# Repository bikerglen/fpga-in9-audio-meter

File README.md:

# fpga-in9-audio-meter
<p>Clone repo to convenient location</p>
<p>Launch Vivado 2018.2</p>
<p>In TCL console:</p>
<p>cd [path to create project]</p>
<p>source [path to repo]/vivado/create-project.tcl</p>
<p>generate bitstream</p>
<p>export hardware / local / do not include bitstream</p>
<p>launch sdk</p>
<p>create new xilinx standalone hello world application</p>
<p>replace helloworld C code with contents of sdk-c/helloworld.c</p>
<p>add 'm' to helloworld -> properties -> C/C++ Build -> Settings -> Libraries
</p>
<p>to do: rewrite cordic using generate loops</p>

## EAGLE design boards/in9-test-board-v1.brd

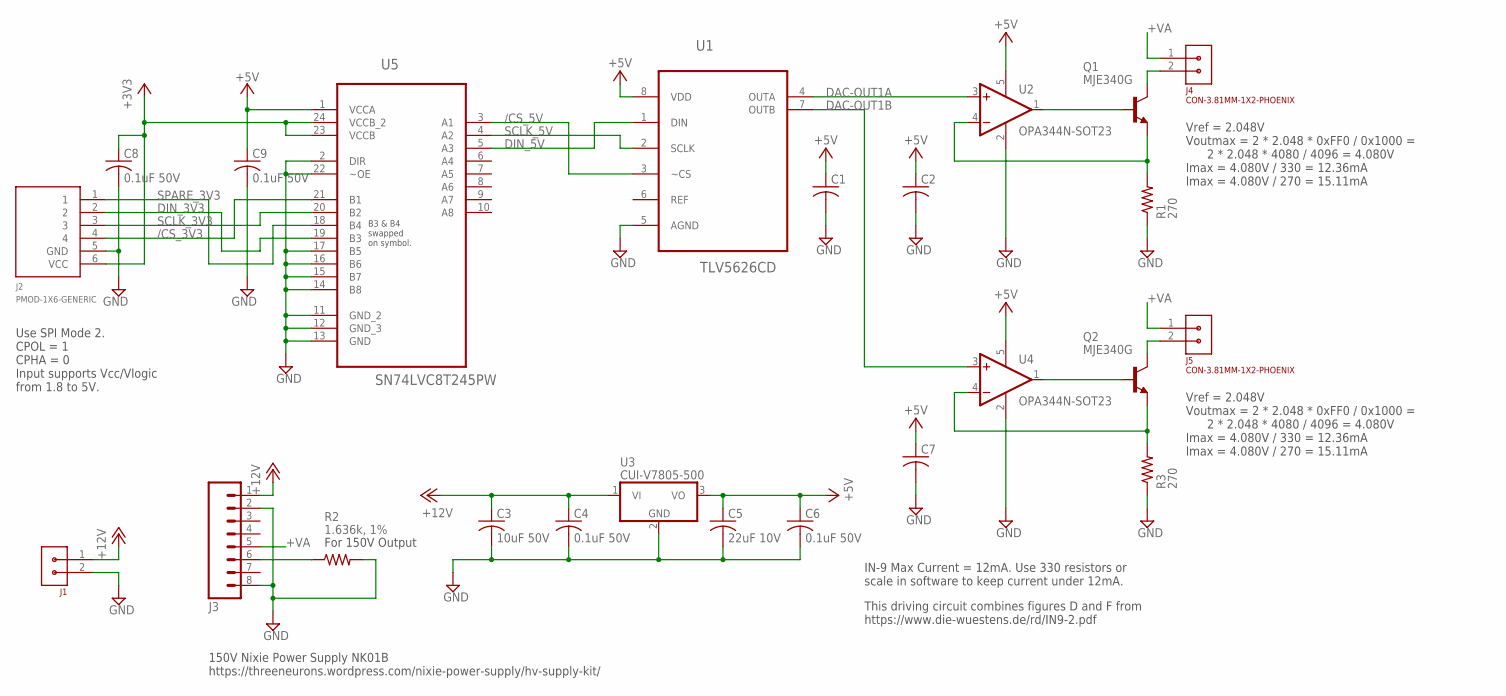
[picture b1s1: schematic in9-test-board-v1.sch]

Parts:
C1, C2, C7: C-USC1206K; C1206K
C3: 10uF 50V; C1210K; MFR_PART_NO C1210C106K5RACTU
C4, C6, C8, C9: 0.1uF 50V; C1206K; MFR_PART_NO C1206S104M5RACTU
C5: 22uF 10V; C1206K; MFR_PART_NO C1206C226K8RAC7800
J1: CON-3.81MM-1X2-PHOENIX-1803426; CON-PHOENIX-1803426-3.81-1X2
J2: PMOD-1X6-GENERIC; CON-PMOD-1X6
J3: M08; 1X08
J4, J5: CON-3.81MM-1X2-PHOENIX; CON-PHOENIX-3.81-1X2-RA
Q1, Q2: MJE340G; TO126V
R1, R3: 270; R1206
R2: 1.636k, 1%; R1206
U1: TLV5626CD; SOIC127P600X175-8N
U2, U4: OPA344N-SOT23; SOT23-5
U3: CUI-V7805-500; CUI-78XX-500
U5: SN74LVC8T245PW; SOP65P640X120-24N

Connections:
+3V3: C8.1, J2.6 (VCC), U5.23 (VCCB), U5.24 (VCCB_2)
+5V: C1.1, C2.1, C5.1, C6.1, C7.1, C9.1, U1.8 (VDD), U2.5 (V+), U3.3 (VO), U4.5 (V+), U5.1 (VCCA)
+12V: C3.1, C4.1, J1.1, J3.1, U3.1 (VI)
+VA: J3.5, J4.1, J5.1
/CS_3V3: J2.4, U5.21 (B1)
/CS_5V: U1.3 (~CS), U5.3 (A1)
DAC-OUT1A: U1.4 (OUTA), U2.3 (+IN)
DAC-OUT1B: U1.7 (OUTB), U4.3 (+IN)
DIN_3V3: J2.2, U5.19 (B3)
DIN_5V: U1.1 (DIN), U5.5 (A3)
GND: C1.2, C2.2, C3.2, C4.2, C5.2, C6.2, C7.2, C8.2, C9.2, J1.2, J2.5 (GND), J3.2, J3.8, R1.1, R2.2, R3.1, U1.5 (AGND), U2.2 (V-), U3.2 (GND), U4.2 (V-), U5.2 (DIR), U5.11 (GND_2), U5.12 (GND_3), U5.13 (GND), U5.14 (B8), U5.15 (B7), U5.16 (B6), U5.17 (B5), U5.22 (~OE)
unnamed: Q1.1 (E), R1.2, U2.4 (-IN)
unnamed: Q1.3 (B), U2.1 (OUT)
unnamed: J3.6, R2.1
unnamed: Q2.1 (E), R3.2, U4.4 (-IN)
unnamed: Q2.3 (B), U4.1 (OUT)
OUT1A: J4.2, Q1.2 (C)
OUT1B: J5.2, Q2.2 (C)
SCLK_3V3: J2.3, U5.20 (B2)
SCLK_5V: U1.2 (SCLK), U5.4 (A2)
SPARE_3V3: J2.1, U5.18 (B4)

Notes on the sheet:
Vref = 2.048V Voutmax = 2 * 2.048 * 0xFF0 / 0x1000 = 2 * 2.048 * 4080 / 4096 = 4.080V Imax = 4.080V / 330 = 12.36mA Imax = 4.080V / 270 = 15.11mA
For 150V Output
150V Nixie Power Supply NK01B https://threeneurons.wordpress.com/nixie-power-supply/hv-supply-kit/
This driving circuit combines figures D and F from https://www.die-wuestens.de/rd/IN9-2.pdf
B3 & B4 swapped on symbol.
Use SPI Mode 2. CPOL = 1 CPHA = 0 Input supports Vcc/Vlogic from 1.8 to 5V.
IN-9 Max Current = 12mA. Use 330 resistors or scale in software to keep current under 12mA.

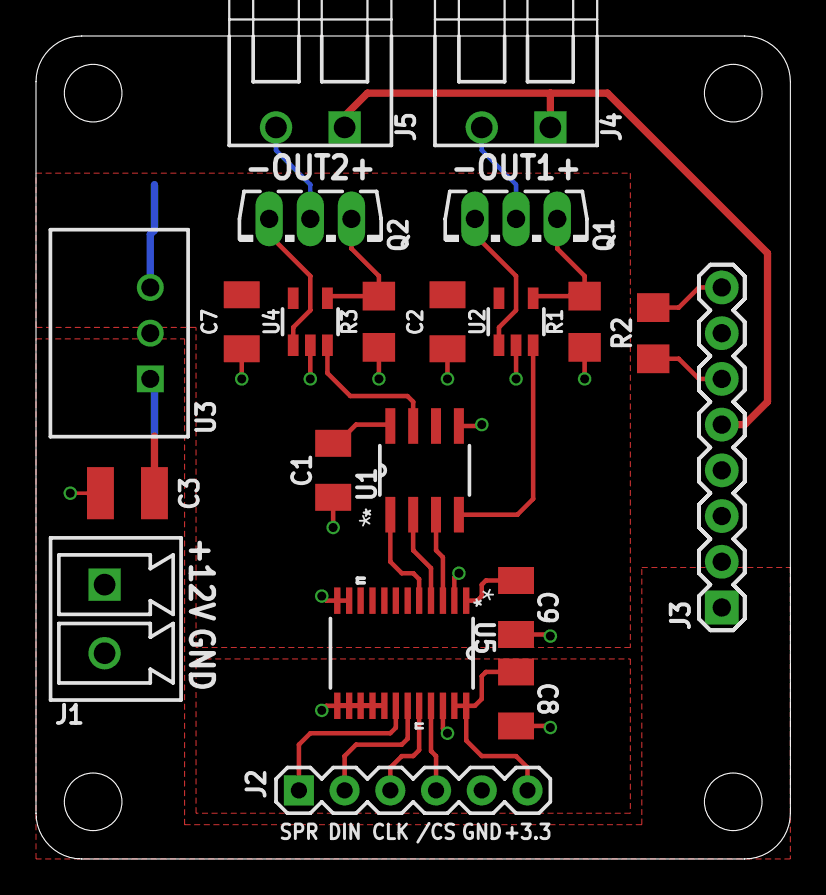
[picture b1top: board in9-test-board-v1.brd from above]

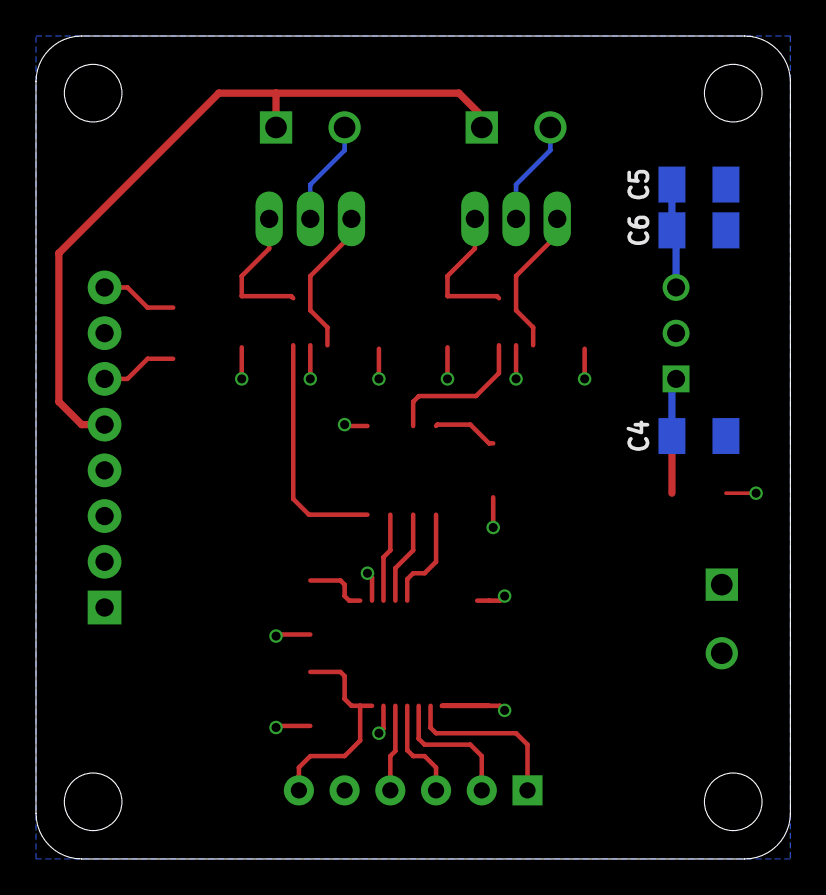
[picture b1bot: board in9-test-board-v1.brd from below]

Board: 2 copper layers, 41.9 x 45.7 mm, 24 parts (3 on the bottom side), 21 nets.

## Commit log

2018-07-03 initial checkin
2018-07-04 forgot GPL text
2018-07-04 formatting
2018-07-04 added -lm switch to sdk build
2019-01-06 added PDFs of schematic and board
2019-01-06 fixed landscape print
